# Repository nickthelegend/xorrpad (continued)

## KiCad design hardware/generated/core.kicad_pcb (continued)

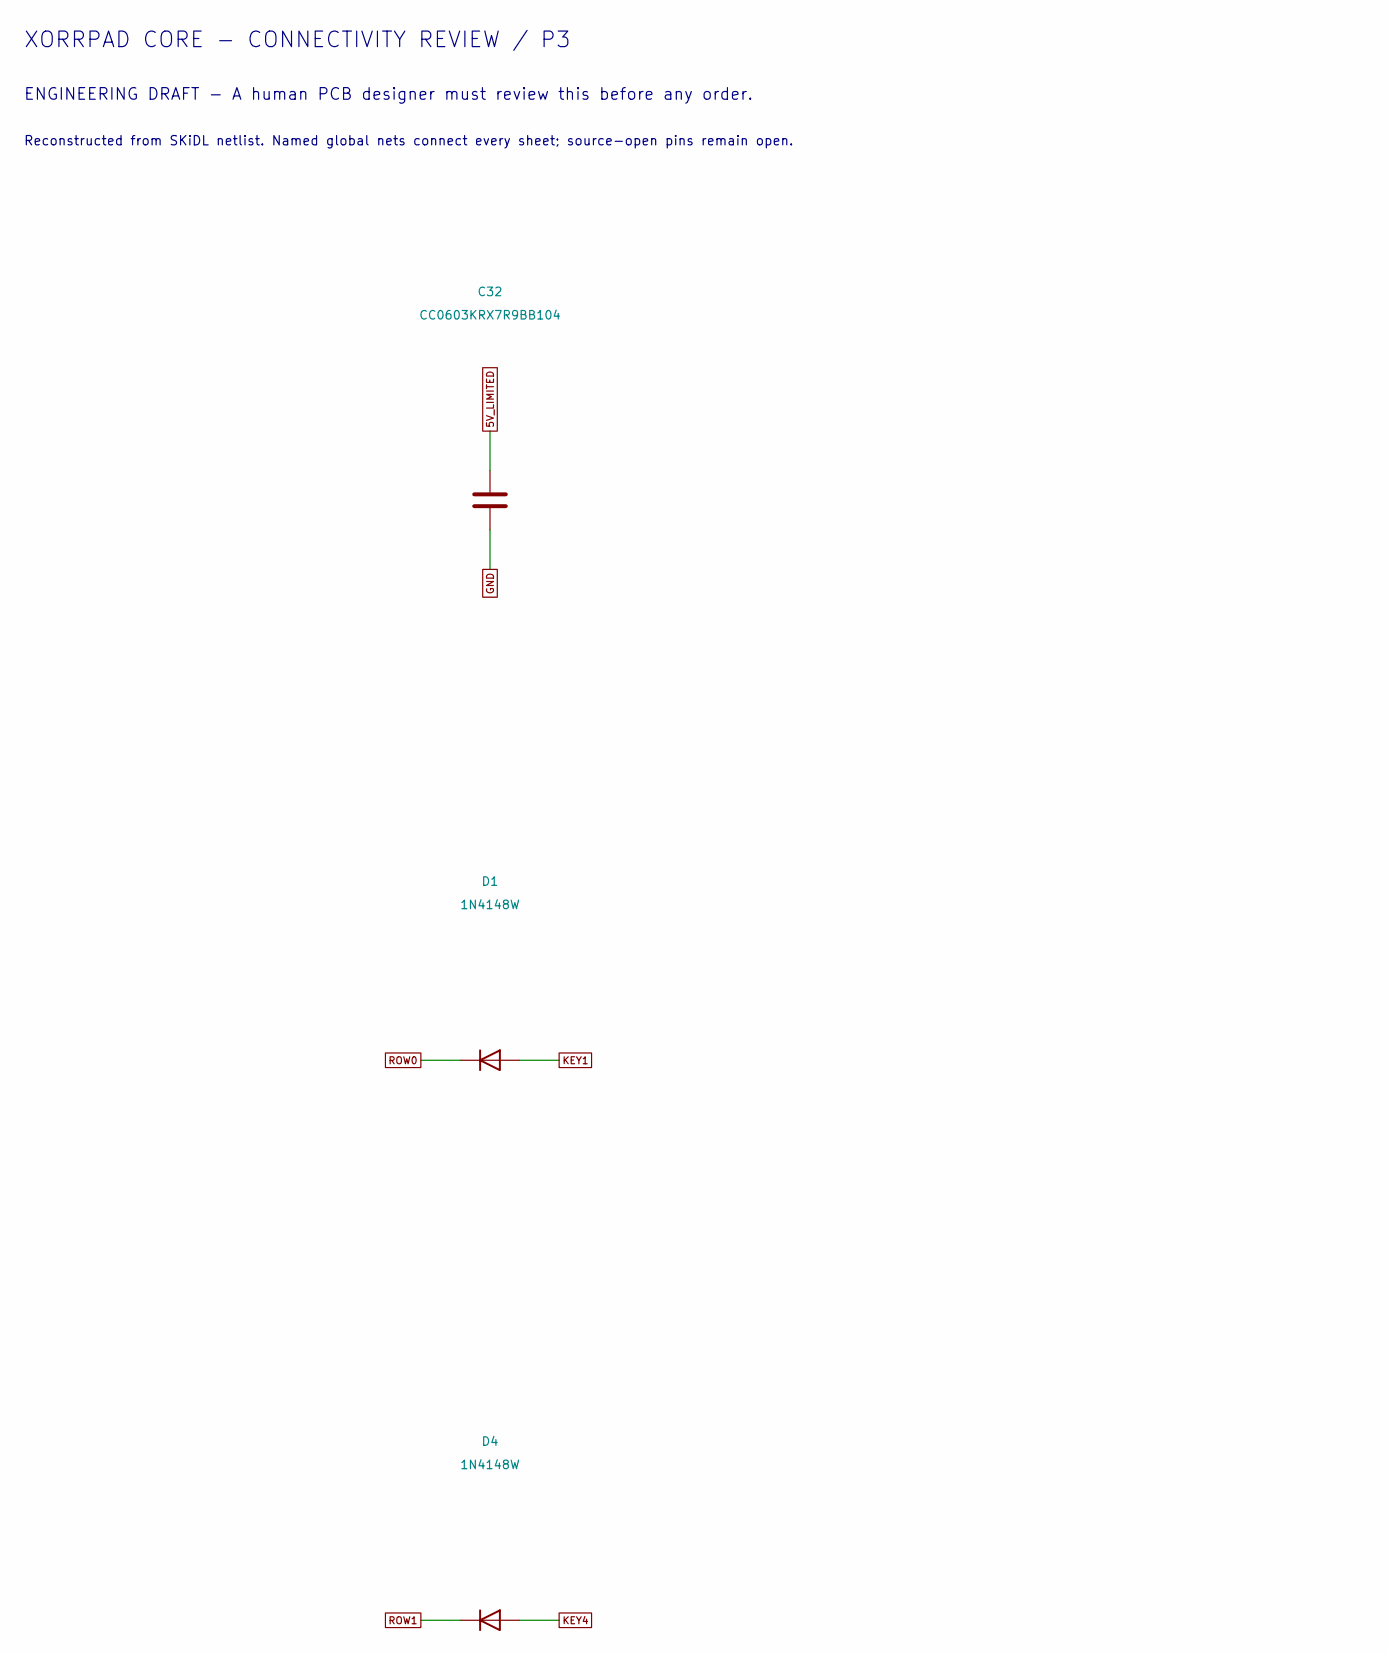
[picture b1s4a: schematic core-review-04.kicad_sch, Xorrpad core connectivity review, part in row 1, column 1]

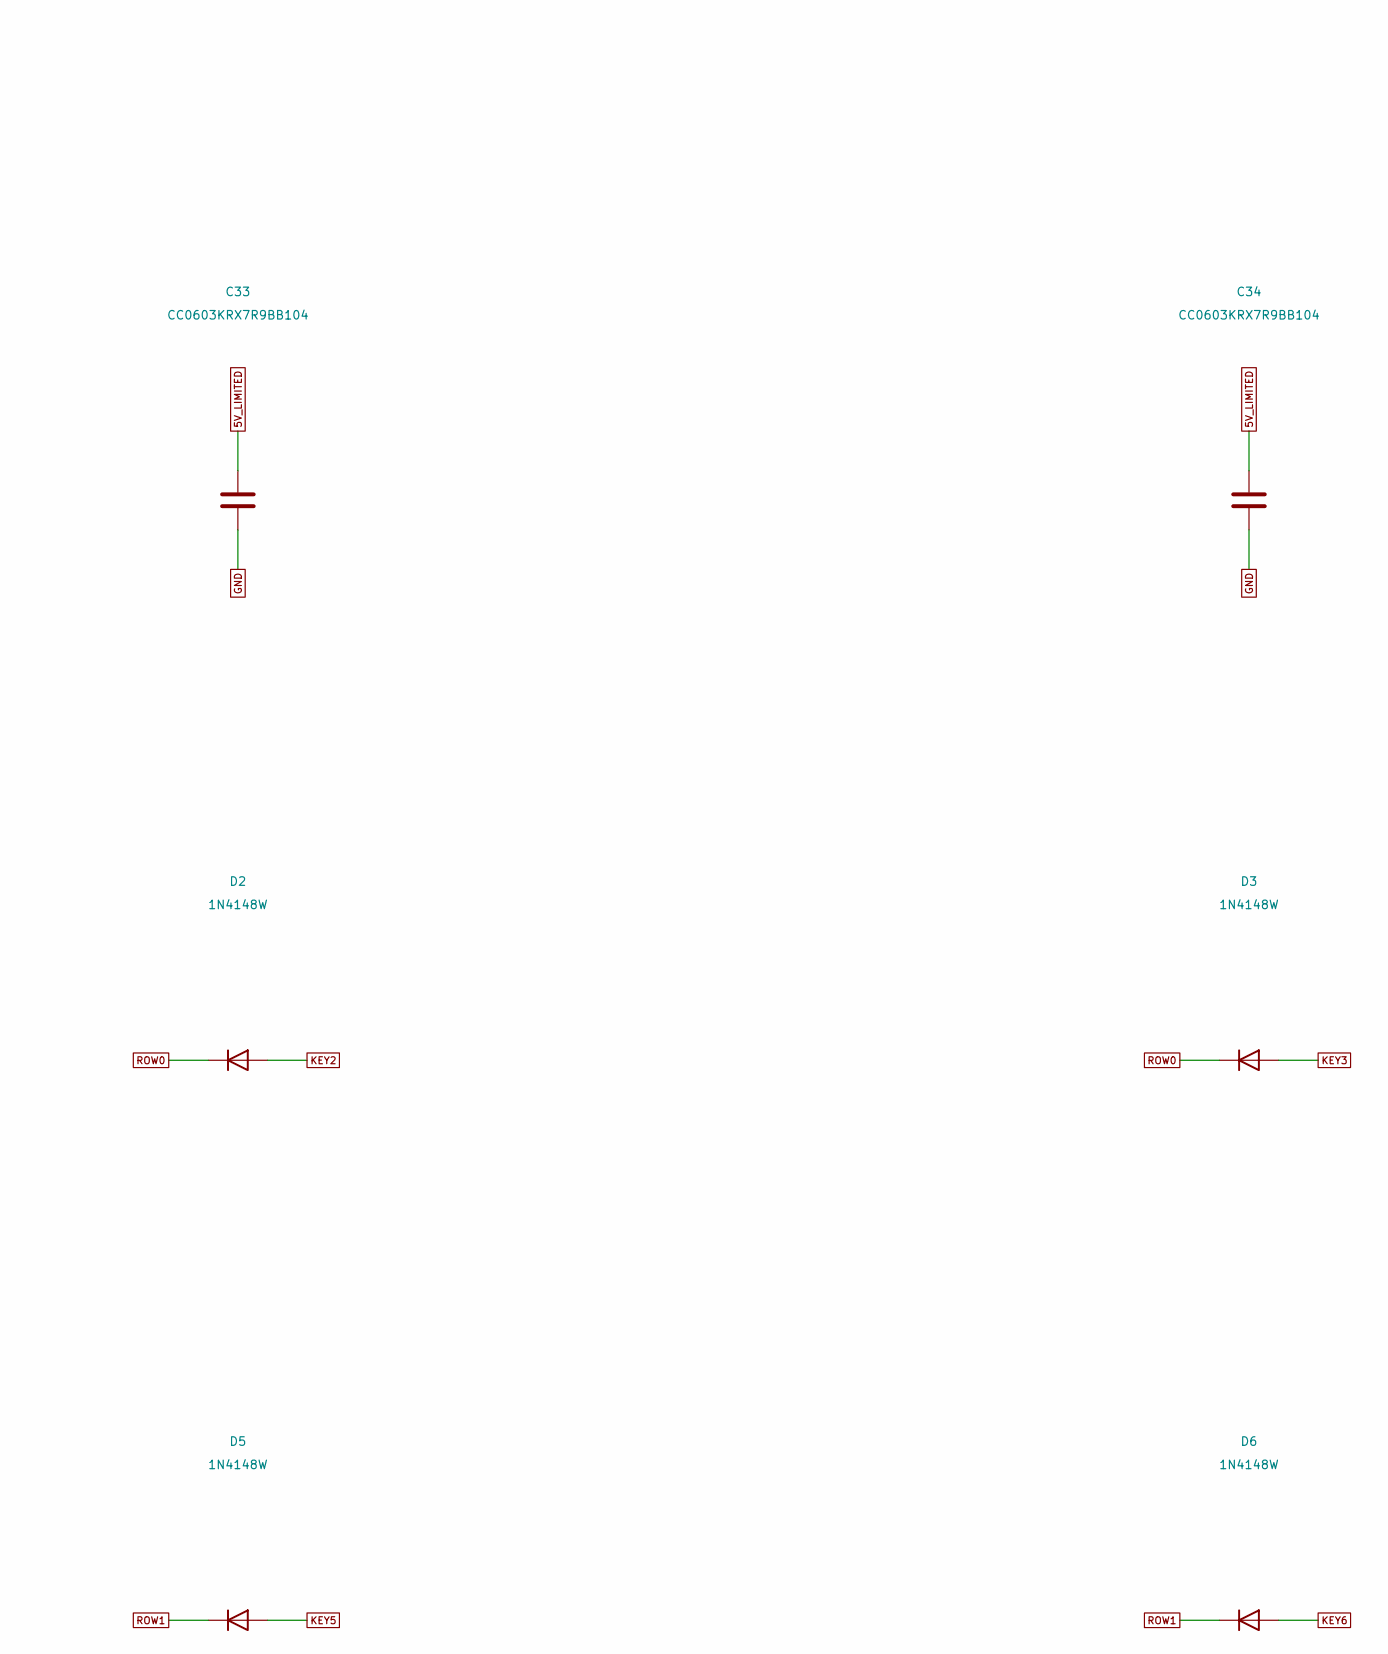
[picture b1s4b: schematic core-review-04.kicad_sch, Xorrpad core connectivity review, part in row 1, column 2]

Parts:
C32, C33, C34: CC0603KRX7R9BB104; C_0603_1608Metric
D1, D2, D3, D4, D5, D6: 1N4148W; D_SOD-123

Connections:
5V_LIMITED: C32.1, C33.1, C34.1; also elsewhere on the board
GND: C32.2, C33.2, C34.2; also elsewhere on the board
KEY1: D1.2 (A); also elsewhere on the board
KEY2: D2.2 (A); also elsewhere on the board
KEY3: D3.2 (A); also elsewhere on the board
KEY4: D4.2 (A); also elsewhere on the board
KEY5: D5.2 (A); also elsewhere on the board
KEY6: D6.2 (A); also elsewhere on the board
ROW0: D1.1 (K), D2.1 (K), D3.1 (K); also elsewhere on the board
ROW1: D4.1 (K), D5.1 (K), D6.1 (K); also elsewhere on the board

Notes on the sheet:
XORRPAD CORE - CONNECTIVITY REVIEW / P3
ENGINEERING DRAFT - A human PCB designer must review this before any order.
Reconstructed from SKiDL netlist. Named global nets connect every sheet; source-open pins remain open.

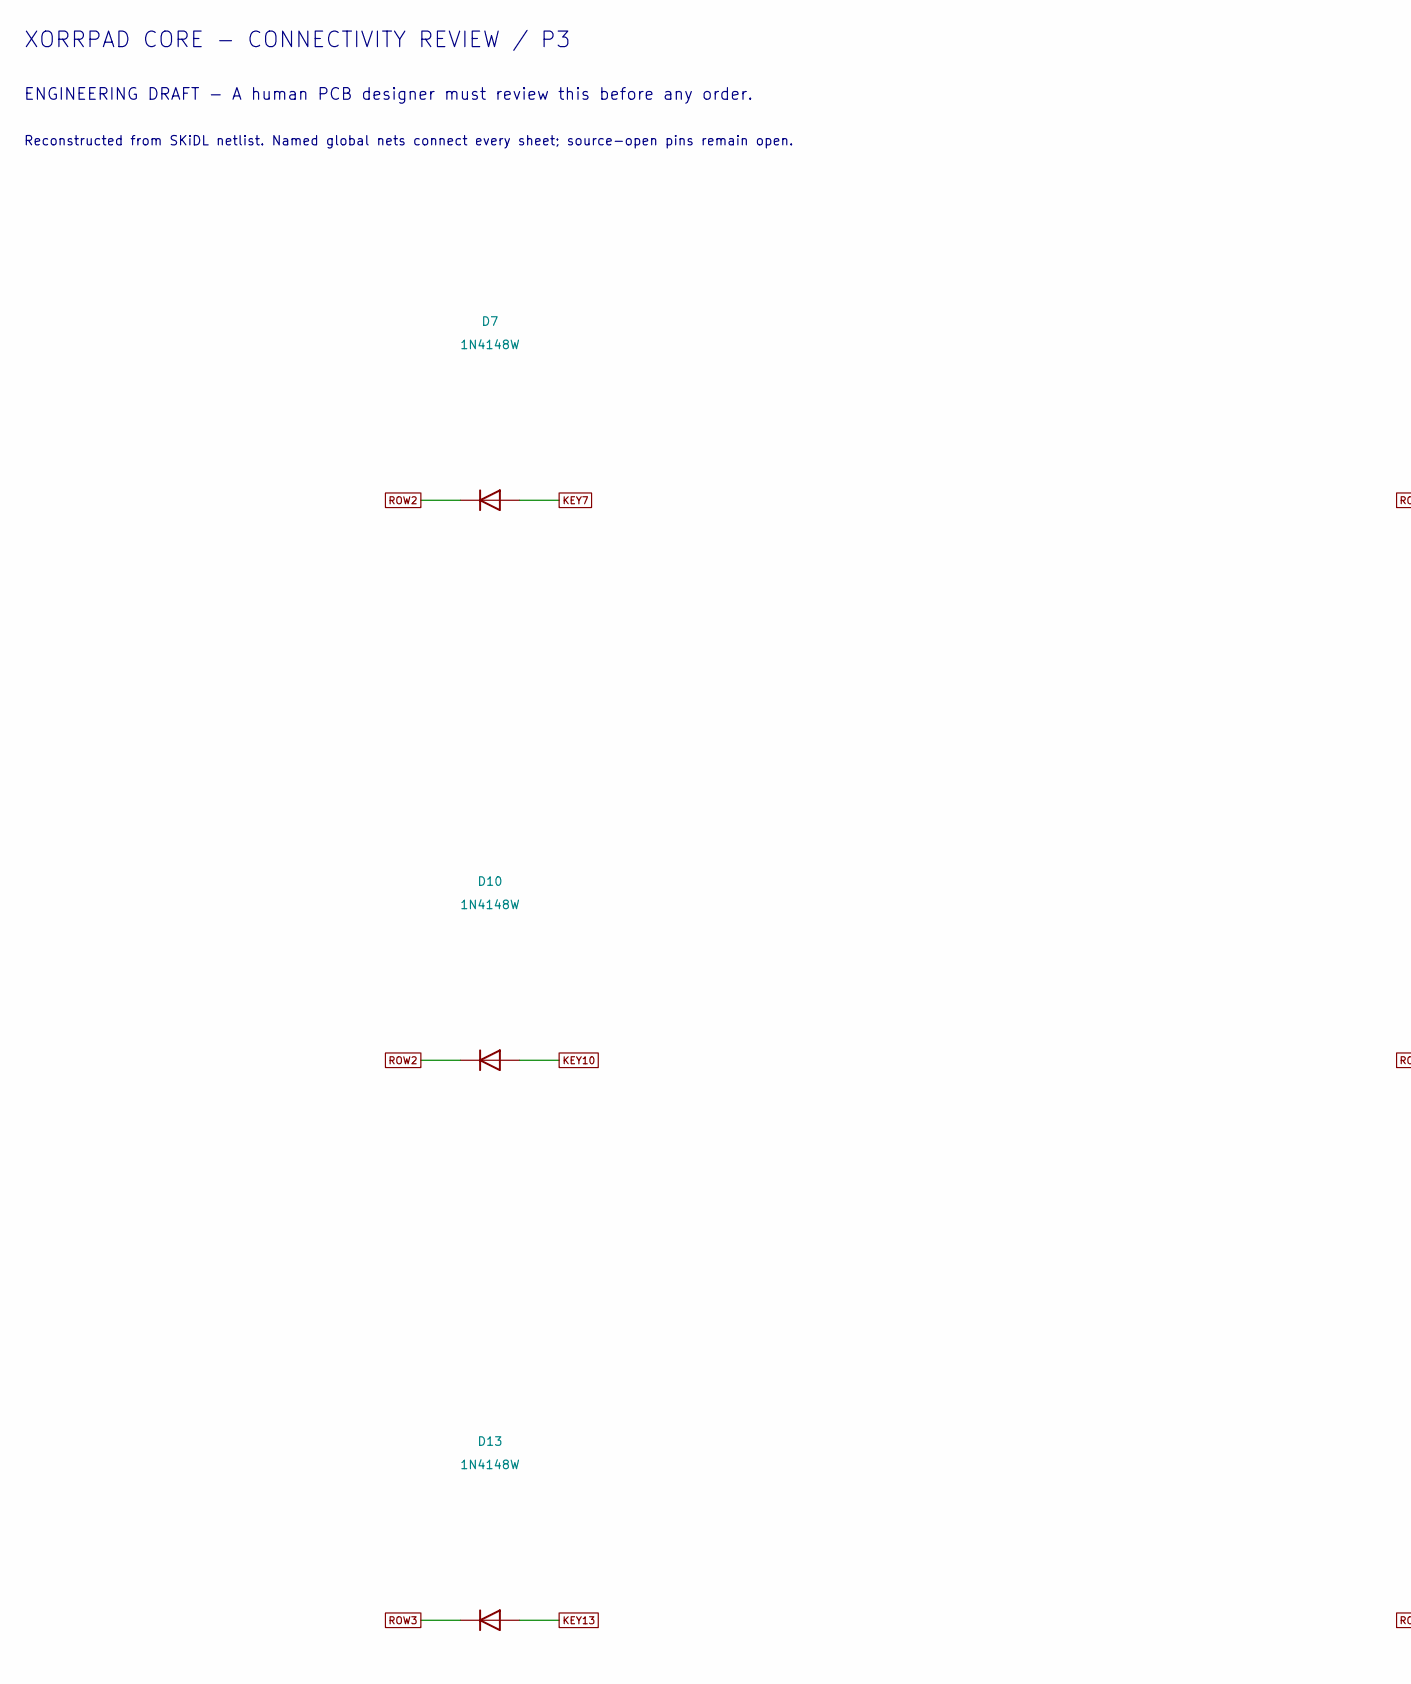
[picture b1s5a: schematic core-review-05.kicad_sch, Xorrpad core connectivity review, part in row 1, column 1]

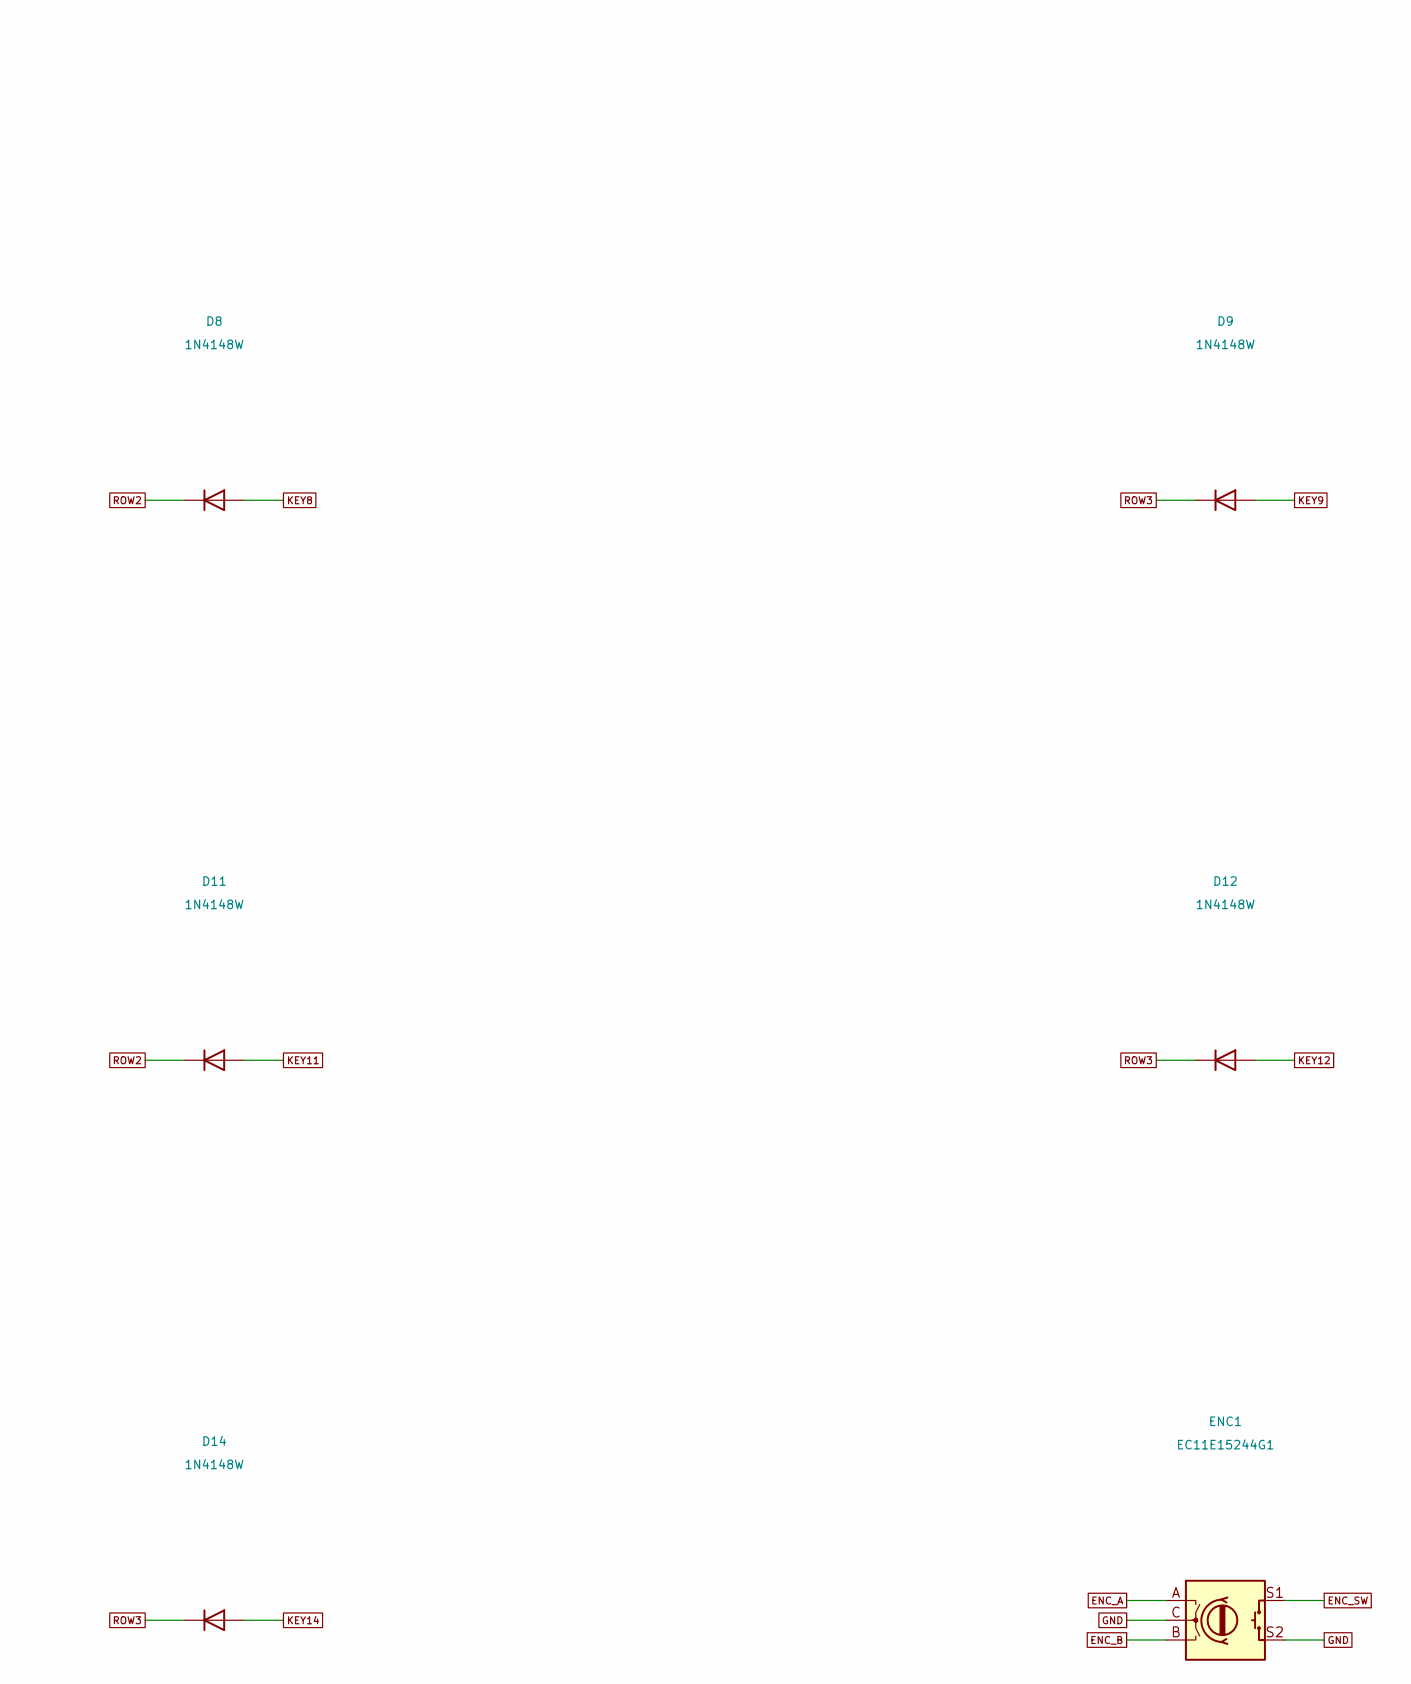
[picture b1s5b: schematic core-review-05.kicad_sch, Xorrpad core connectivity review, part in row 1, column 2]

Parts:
D7, D8, D9, D10, D11, D12, D13, D14: 1N4148W; D_SOD-123
ENC1: EC11E15244G1; RotaryEncoder_Alps_EC11E-Switch_Vertical_H20mm

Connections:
ENC_A: ENC1.A; also elsewhere on the board
ENC_B: ENC1.B; also elsewhere on the board
ENC_SW: ENC1.S1; also elsewhere on the board
GND: ENC1.C, ENC1.S2; also elsewhere on the board
KEY7: D7.2 (A); also elsewhere on the board
KEY8: D8.2 (A); also elsewhere on the board
KEY9: D9.2 (A); also elsewhere on the board
KEY10: D10.2 (A); also elsewhere on the board
KEY11: D11.2 (A); also elsewhere on the board
KEY12: D12.2 (A); also elsewhere on the board
KEY13: D13.2 (A); also elsewhere on the board
KEY14: D14.2 (A); also elsewhere on the board
ROW2: D7.1 (K), D8.1 (K), D10.1 (K), D11.1 (K); also elsewhere on the board
ROW3: D9.1 (K), D12.1 (K), D13.1 (K), D14.1 (K); also elsewhere on the board

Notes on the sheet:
XORRPAD CORE - CONNECTIVITY REVIEW / P3
ENGINEERING DRAFT - A human PCB designer must review this before any order.
Reconstructed from SKiDL netlist. Named global nets connect every sheet; source-open pins remain open.

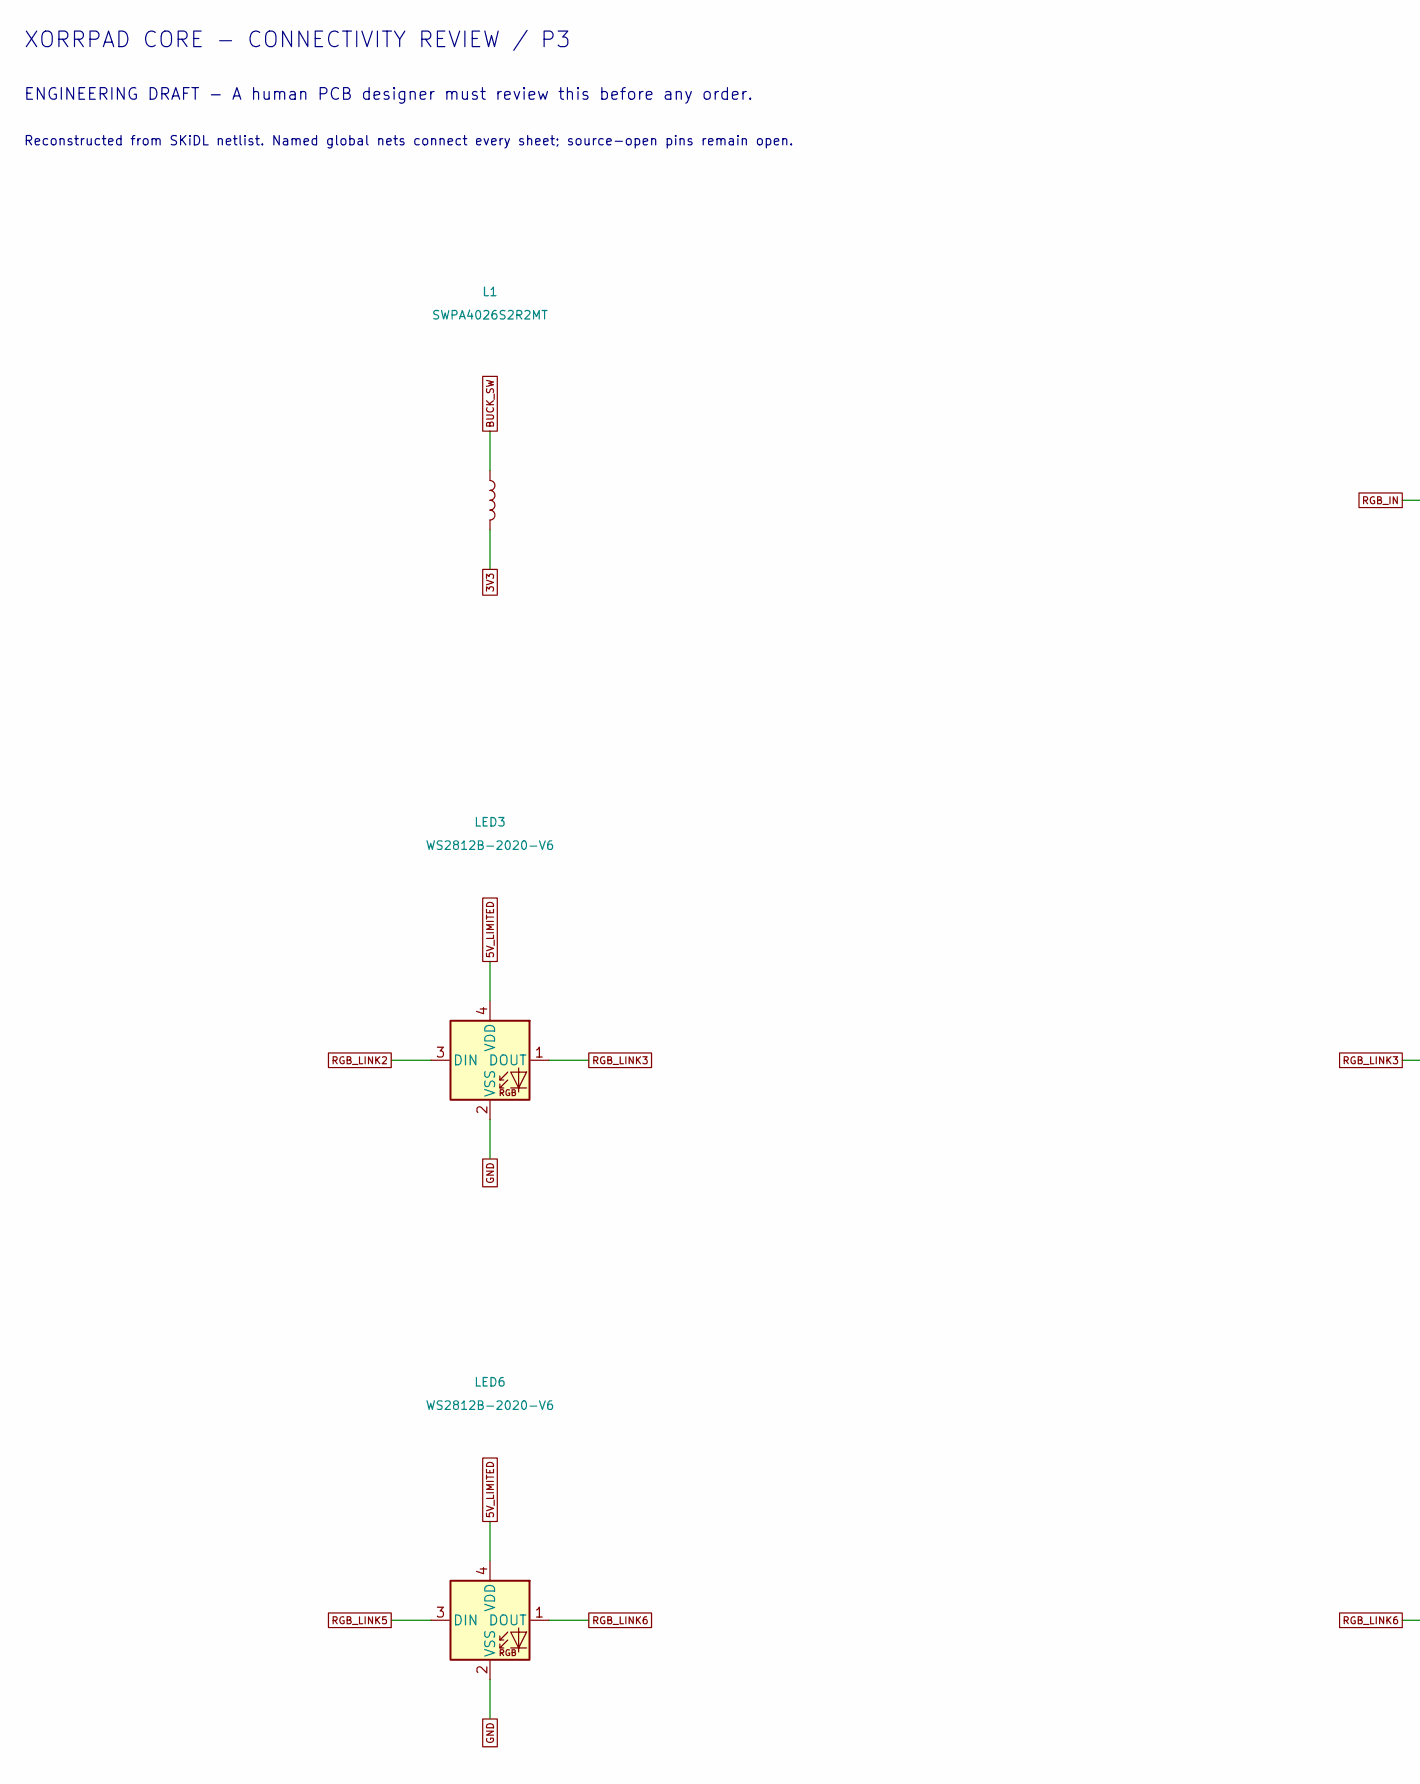
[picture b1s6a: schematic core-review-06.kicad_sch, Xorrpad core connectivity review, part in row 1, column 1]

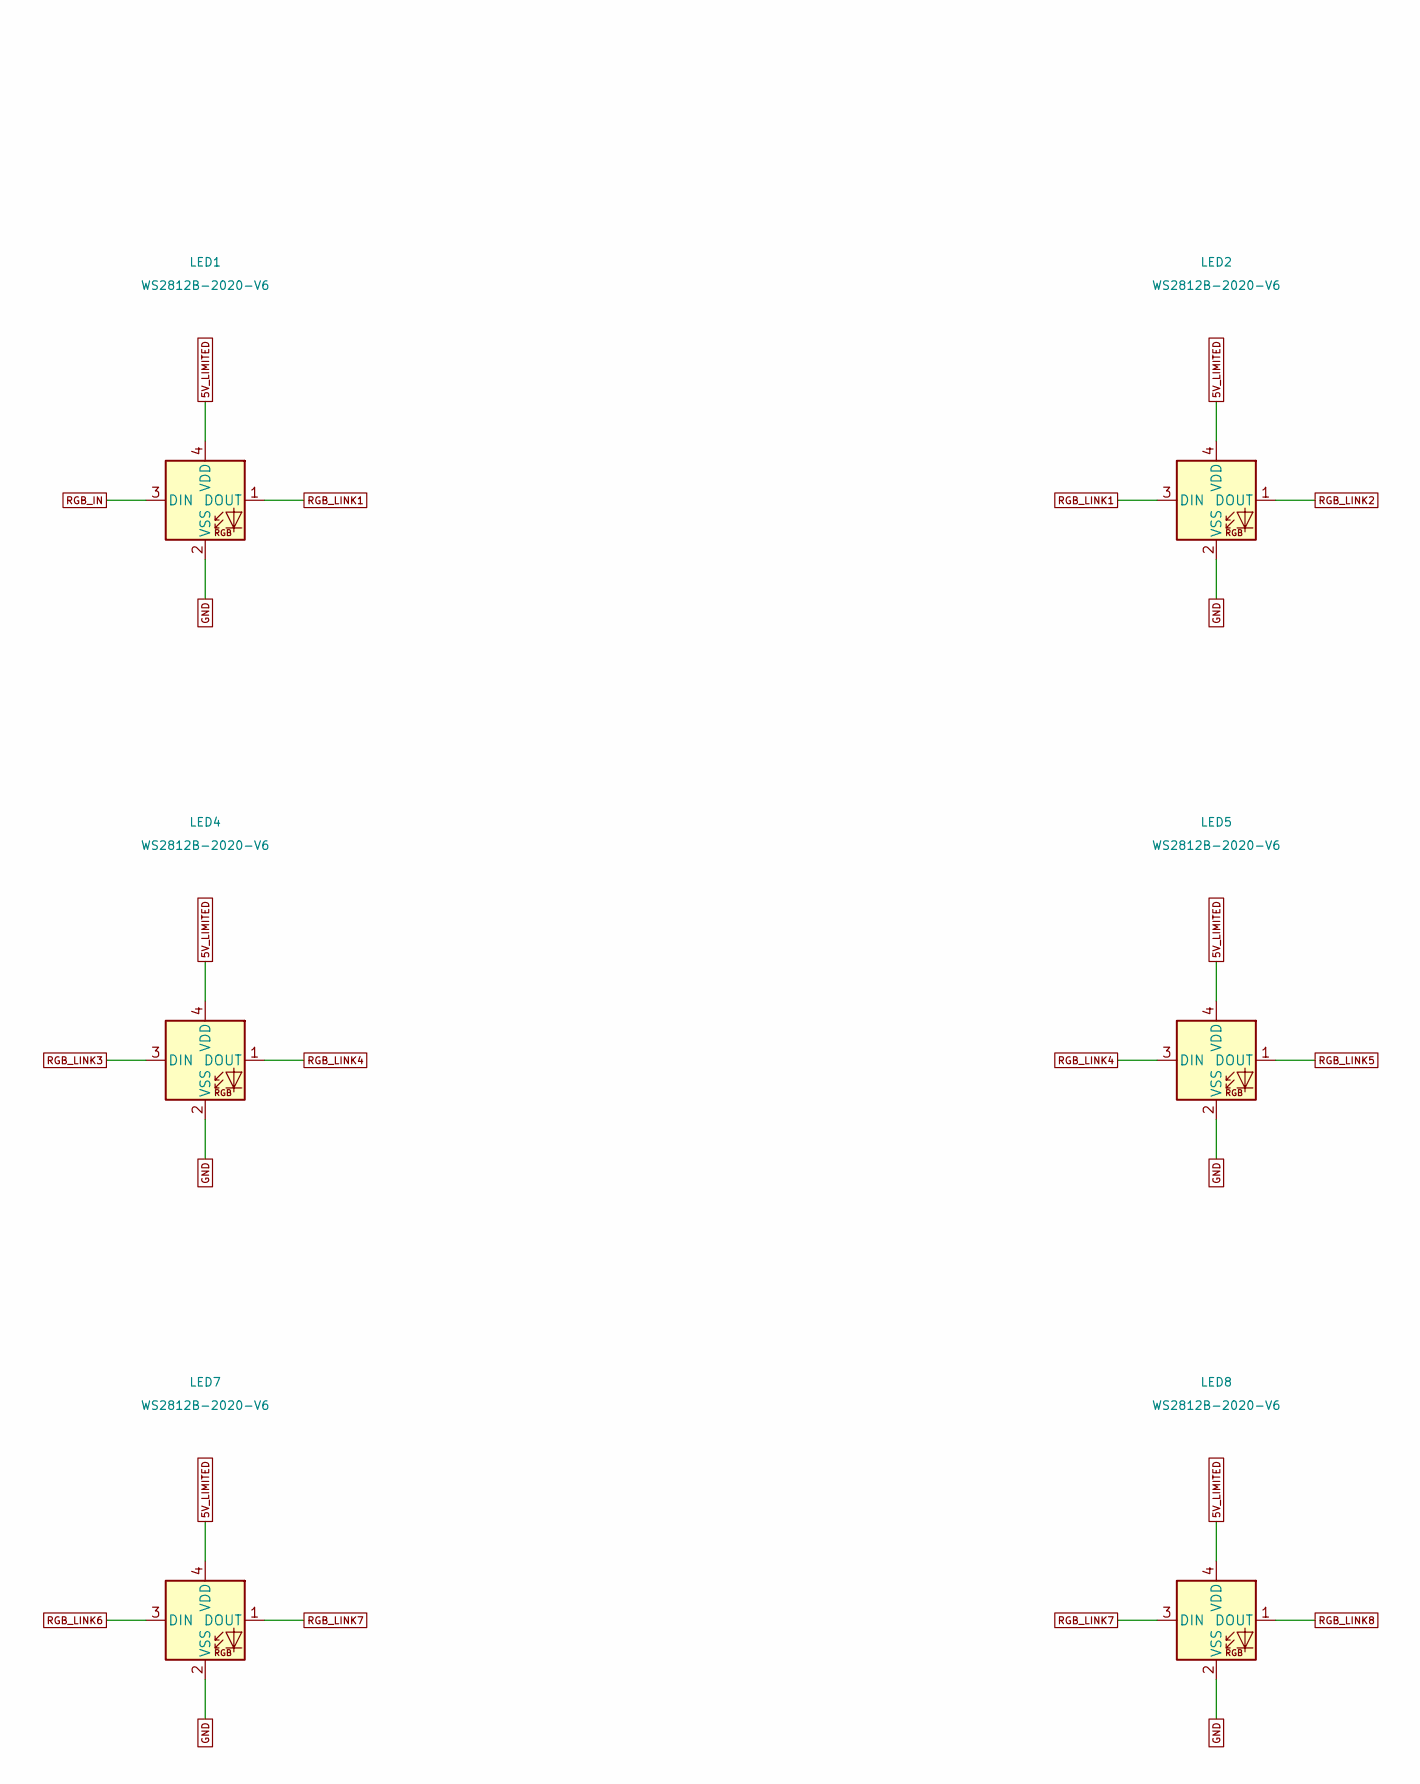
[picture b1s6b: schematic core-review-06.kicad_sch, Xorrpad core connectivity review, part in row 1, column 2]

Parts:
L1: SWPA4026S2R2MT; L_Sunlord_SWPA4026S
LED1, LED2, LED3, LED4, LED5, LED6, LED7, LED8: WS2812B-2020-V6; LED_WS2812B-2020_PLCC4_2.0x2.0mm

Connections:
3V3: L1.2; also elsewhere on the board
5V_LIMITED: LED1.4 (VDD), LED2.4 (VDD), LED3.4 (VDD), LED4.4 (VDD), LED5.4 (VDD), LED6.4 (VDD), LED7.4 (VDD), LED8.4 (VDD); also elsewhere on the board
BUCK_SW: L1.1; also elsewhere on the board
GND: LED1.2 (VSS), LED2.2 (VSS), LED3.2 (VSS), LED4.2 (VSS), LED5.2 (VSS), LED6.2 (VSS), LED7.2 (VSS), LED8.2 (VSS); also elsewhere on the board
RGB_IN: LED1.3 (DIN); also elsewhere on the board
RGB_LINK1: LED1.1 (DOUT), LED2.3 (DIN)
RGB_LINK2: LED2.1 (DOUT), LED3.3 (DIN)
RGB_LINK3: LED3.1 (DOUT), LED4.3 (DIN)
RGB_LINK4: LED4.1 (DOUT), LED5.3 (DIN)
RGB_LINK5: LED5.1 (DOUT), LED6.3 (DIN)
RGB_LINK6: LED6.1 (DOUT), LED7.3 (DIN)
RGB_LINK7: LED7.1 (DOUT), LED8.3 (DIN)
RGB_LINK8: LED8.1 (DOUT); also elsewhere on the board

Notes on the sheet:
XORRPAD CORE - CONNECTIVITY REVIEW / P3
ENGINEERING DRAFT - A human PCB designer must review this before any order.
Reconstructed from SKiDL netlist. Named global nets connect every sheet; source-open pins remain open.

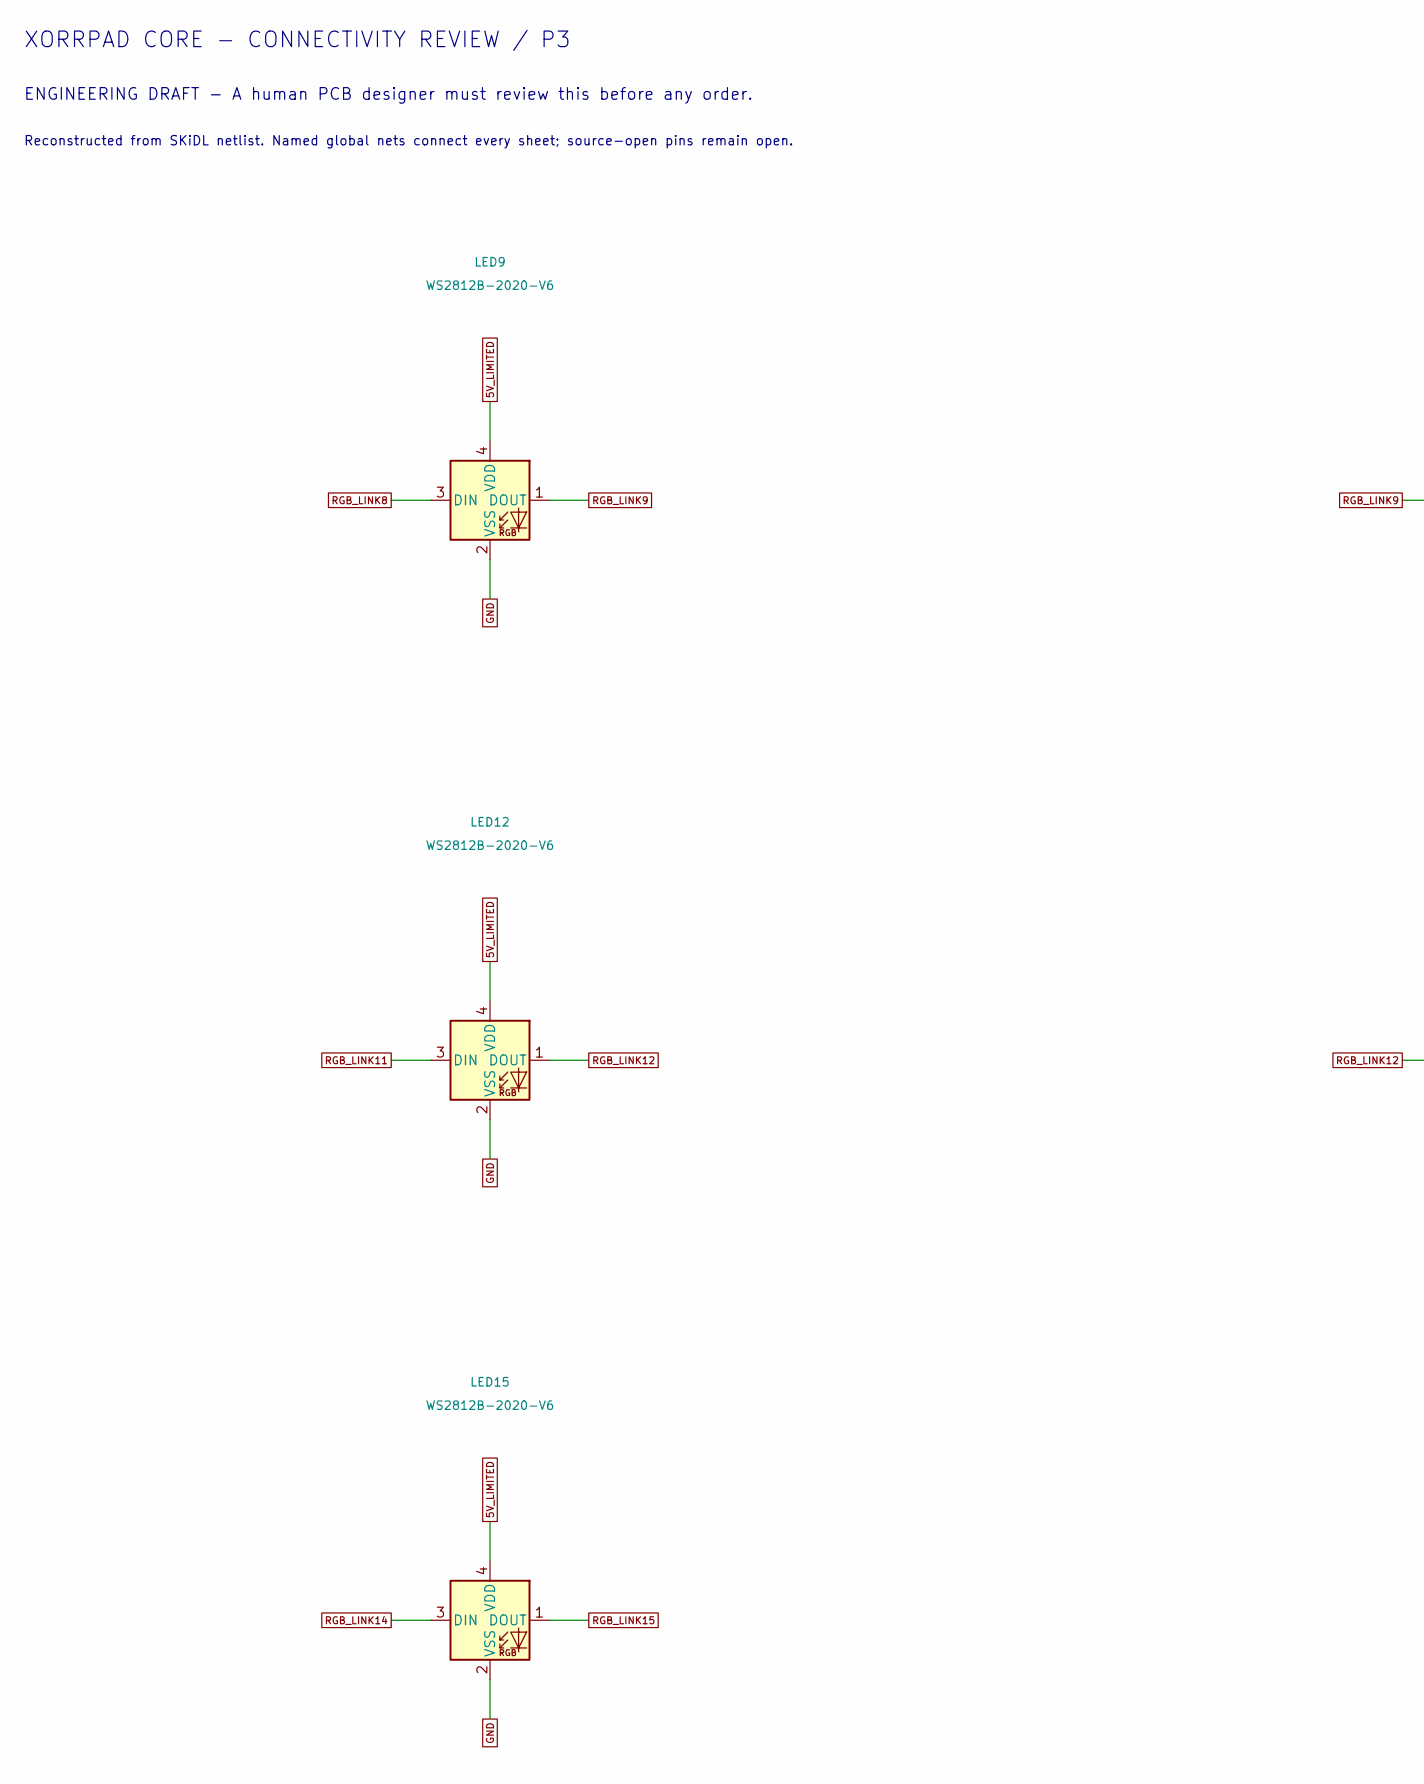
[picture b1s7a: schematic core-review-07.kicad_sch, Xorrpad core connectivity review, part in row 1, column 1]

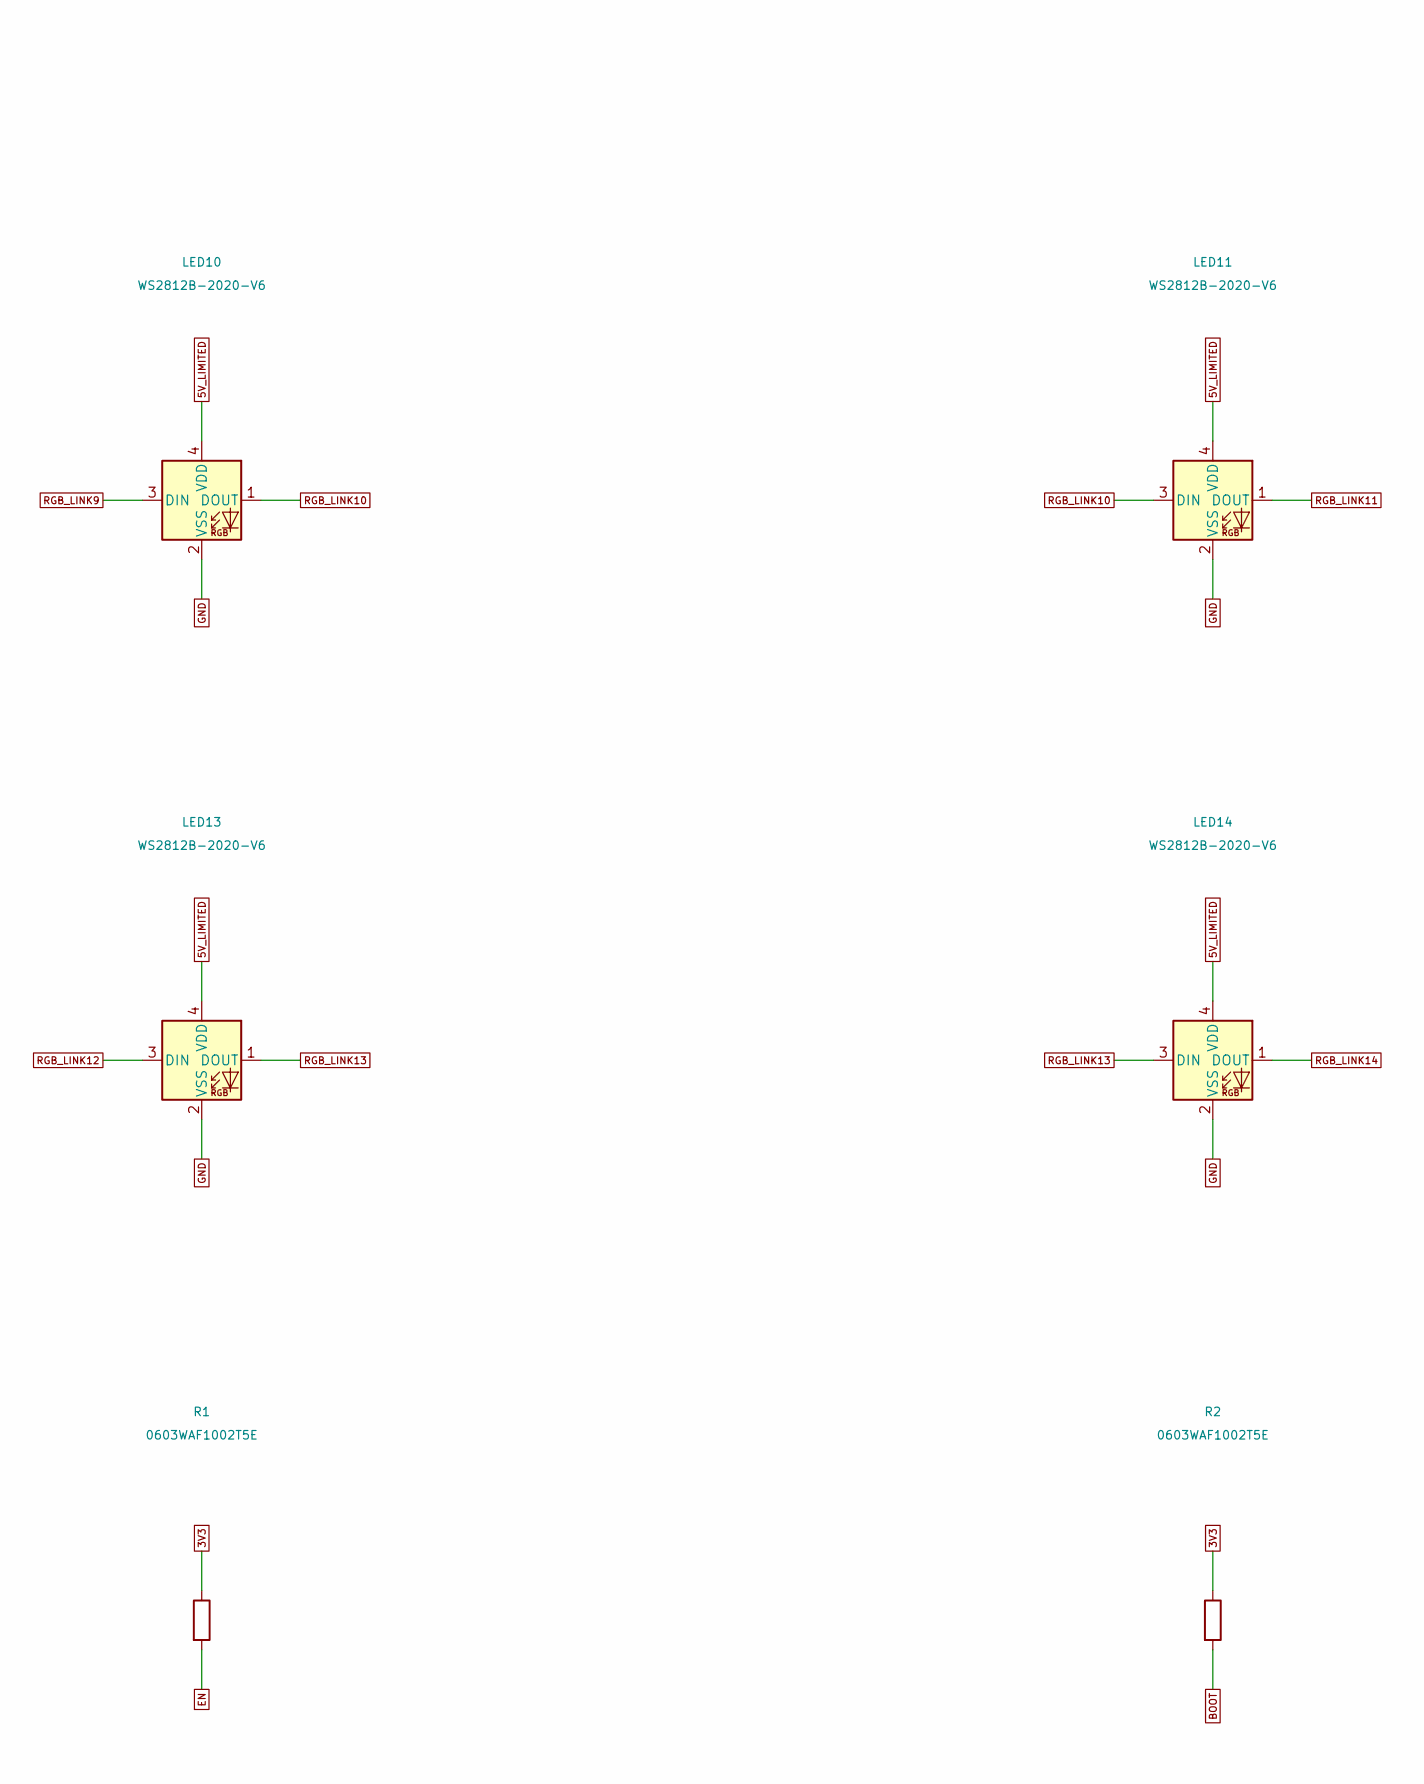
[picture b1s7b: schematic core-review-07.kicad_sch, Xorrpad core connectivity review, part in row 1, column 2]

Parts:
LED9, LED10, LED11, LED12, LED13, LED14, LED15: WS2812B-2020-V6; LED_WS2812B-2020_PLCC4_2.0x2.0mm
R1, R2: 0603WAF1002T5E; R_0603_1608Metric

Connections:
3V3: R1.1, R2.1; also elsewhere on the board
5V_LIMITED: LED9.4 (VDD), LED10.4 (VDD), LED11.4 (VDD), LED12.4 (VDD), LED13.4 (VDD), LED14.4 (VDD), LED15.4 (VDD); also elsewhere on the board
BOOT: R2.2; also elsewhere on the board
EN: R1.2; also elsewhere on the board
GND: LED9.2 (VSS), LED10.2 (VSS), LED11.2 (VSS), LED12.2 (VSS), LED13.2 (VSS), LED14.2 (VSS), LED15.2 (VSS); also elsewhere on the board
RGB_LINK8: LED9.3 (DIN); also elsewhere on the board
RGB_LINK9: LED9.1 (DOUT), LED10.3 (DIN)
RGB_LINK10: LED10.1 (DOUT), LED11.3 (DIN)
RGB_LINK11: LED11.1 (DOUT), LED12.3 (DIN)
RGB_LINK12: LED12.1 (DOUT), LED13.3 (DIN)
RGB_LINK13: LED13.1 (DOUT), LED14.3 (DIN)
RGB_LINK14: LED14.1 (DOUT), LED15.3 (DIN)
RGB_LINK15: LED15.1 (DOUT)

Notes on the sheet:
XORRPAD CORE - CONNECTIVITY REVIEW / P3
ENGINEERING DRAFT - A human PCB designer must review this before any order.
Reconstructed from SKiDL netlist. Named global nets connect every sheet; source-open pins remain open.
